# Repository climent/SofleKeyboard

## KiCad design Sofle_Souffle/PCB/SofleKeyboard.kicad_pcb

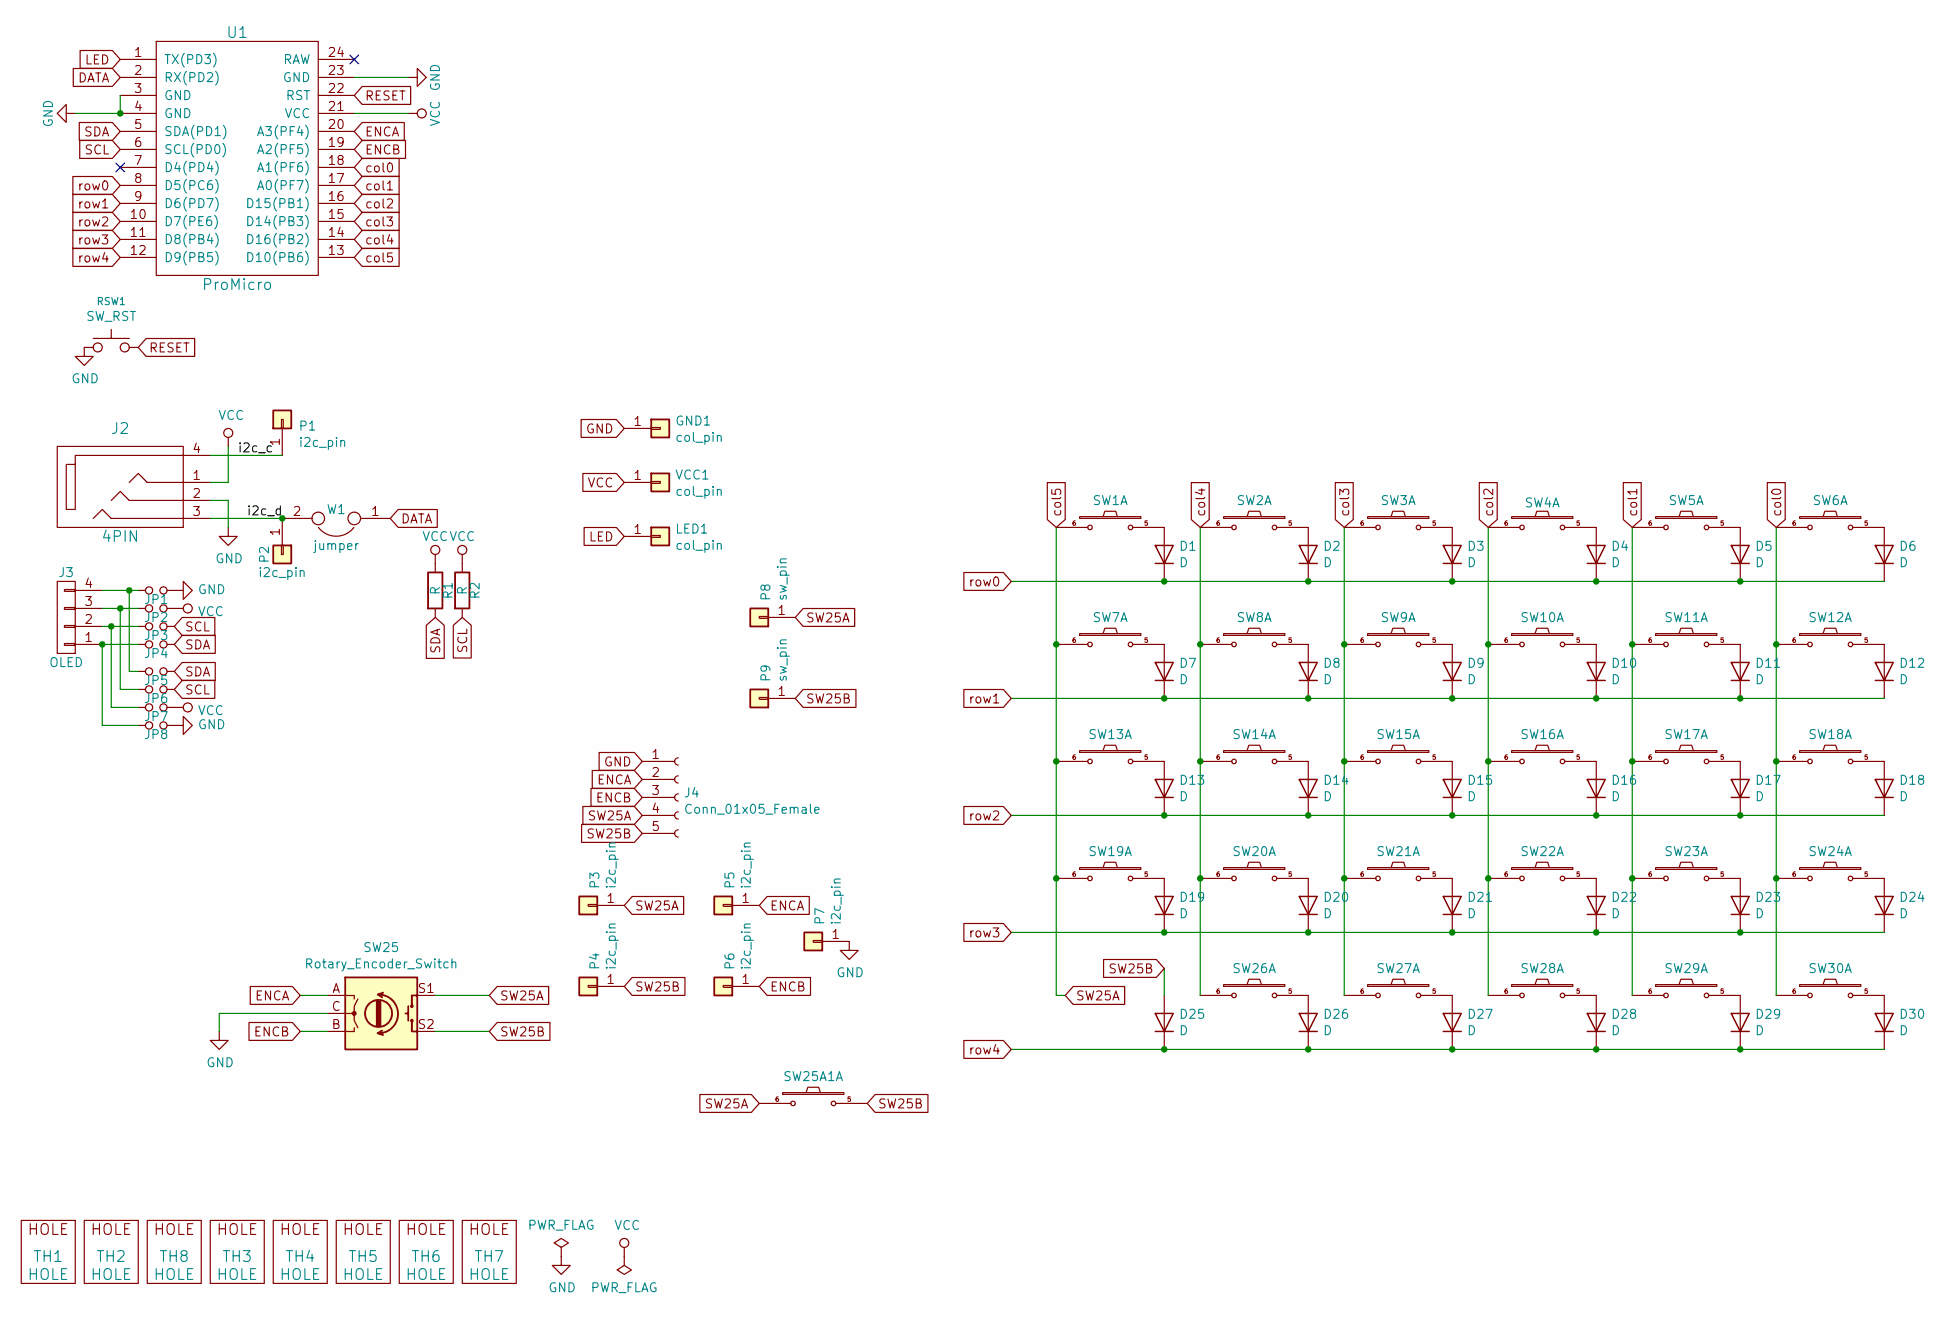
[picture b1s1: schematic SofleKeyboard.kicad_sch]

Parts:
D1, D2, D3, D4, D5, D6, D7, D8, D9, D10, D11, D12, D13, D14, D15, D16, D17, D18, D19, D20, D21, D22, D23, D24, D25, D26, D27, D28, D29, D30: D; crkbd-diode
GND1: col_pin; 1pin_conn
J2: 4PIN; MJ-4PP-9
J3: OLED; OLED_4Pin
J4: Conn_01x05_Female; PinHeader_1x05_P2.54mm_Horizontal
JP1, JP2, JP3, JP4, JP5, JP6, JP7, JP8: Jumper_NO_Small; Jumper
LED1: col_pin; 1pin_conn
P1, P2, P3, P4, P5, P6, P7: i2c_pin; 1pin_conn
P8, P9: sw_pin; Single_Hole
R1, R2: R; RESISTOR_mini
RSW1: SW_RST; TACT_SWITCH_TVBP06
SW1, SW2, SW3, SW4, SW5, SW6, SW7, SW8, SW9, SW10, SW11, SW12, SW13, SW14, SW15, SW16, SW17, SW18, SW19, SW20, SW21, SW22, SW23, SW24, SW25A1, SW26, SW27, SW28, SW29, SW30: SW_PUSH-MX_W_LED; SK6812MINI_and_cherry_NoLEDPads
SW25: Rotary_Encoder_Switch; RotaryEncoder_Alps_EC11E-Switch_Vertical_H20mm-keebio_modif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
TH1, TH2, TH8: HOLE; M2_HOLE_PCB
TH3, TH4, TH5, TH6, TH7: HOLE; HOLE_M2_TH
U1: ProMicro
VCC1: col_pin; 1pin_conn
W1: jumper; jumper_data

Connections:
/i2c_c: J2.4, P1.1; also elsewhere on the board
/i2c_d: J2.3, P2.1, W1.2; also elsewhere on the board
DATA: U1.2 (RX(PD2)), W1.1
ENCA: J4.2, P5.1, SW25.A, U1.20 (A3(PF4))
ENCB: J4.3, P6.1, SW25.B, U1.19 (A2(PF5))
GND: GND1.1, J2.2, J4.1, JP1.2, JP8.2, P7.1, RSW1.1, SW25.C, U1.3 (GND), U1.4 (GND), U1.23 (GND)
LED: LED1.1, U1.1 (TX(PD3))
unnamed: D1.2 (A), SW1.5
unnamed: D2.2 (A), SW2.5
unnamed: D3.2 (A), SW3.5
unnamed: D4.2 (A), SW4.5
unnamed: D5.2 (A), SW5.5
unnamed: D6.2 (A), SW6.5
unnamed: D7.2 (A), SW7.5
unnamed: D8.2 (A), SW8.5
unnamed: D9.2 (A), SW9.5
unnamed: D10.2 (A), SW10.5
unnamed: D11.2 (A), SW11.5
unnamed: D12.2 (A), SW12.5
unnamed: D13.2 (A), SW13.5
unnamed: D14.2 (A), SW14.5
unnamed: D15.2 (A), SW15.5
unnamed: D16.2 (A), SW16.5
unnamed: D17.2 (A), SW17.5
unnamed: D18.2 (A), SW18.5
unnamed: D19.2 (A), SW19.5
unnamed: D20.2 (A), SW20.5
unnamed: D21.2 (A), SW21.5
unnamed: D22.2 (A), SW22.5
unnamed: D23.2 (A), SW23.5
unnamed: D24.2 (A), SW24.5
unnamed: D26.2 (A), SW26.5
unnamed: D27.2 (A), SW27.5
unnamed: D28.2 (A), SW28.5
unnamed: D29.2 (A), SW29.5
unnamed: D30.2 (A), SW30.5
unnamed: J3.1, JP4.1, JP8.1
unnamed: J3.2, JP3.1, JP7.1
unnamed: J3.3, JP2.1, JP6.1
unnamed: J3.4, JP1.1, JP5.1
RESET: RSW1.2, U1.22 (RST)
SCL: JP3.2, JP6.2, R2.2, U1.6 (SCL(PD0)); also elsewhere on the board
SDA: JP4.2, JP5.2, R1.2, U1.5 (SDA(PD1)); also elsewhere on the board
SW25A: J4.4, P3.1, P8.1, SW1.6, SW7.6, SW13.6, SW19.6, SW25.S1, SW25A1.6, U1.13 (D10(PB6))
SW25B: D25.2 (A), J4.5, P4.1, P9.1, SW25.S2, SW25A1.5
VCC: J2.1, JP2.2, JP7.2, R1.1, R2.1, U1.21 (VCC), VCC1.1
col0: SW6.6, SW12.6, SW18.6, SW24.6, SW30.6, U1.18 (A1(PF6))
col1: SW5.6, SW11.6, SW17.6, SW23.6, SW29.6, U1.17 (A0(PF7))
col2: SW4.6, SW10.6, SW16.6, SW22.6, SW28.6, U1.16 (D15(PB1))
col3: SW3.6, SW9.6, SW15.6, SW21.6, SW27.6, U1.15 (D14(PB3))
col4: SW2.6, SW8.6, SW14.6, SW20.6, SW26.6, U1.14 (D16(PB2))
row0: D1.1 (K), D2.1 (K), D3.1 (K), D4.1 (K), D5.1 (K), D6.1 (K), U1.8 (D5(PC6))
row1: D7.1 (K), D8.1 (K), D9.1 (K), D10.1 (K), D11.1 (K), D12.1 (K), U1.9 (D6(PD7))
row2: D13.1 (K), D14.1 (K), D15.1 (K), D16.1 (K), D17.1 (K), D18.1 (K), U1.10 (D7(PE6))
row3: D19.1 (K), D20.1 (K), D21.1 (K), D22.1 (K), D23.1 (K), D24.1 (K), U1.11 (D8(PB4))
row4: D25.1 (K), D26.1 (K), D27.1 (K), D28.1 (K), D29.1 (K), D30.1 (K), U1.12 (D9(PB5))

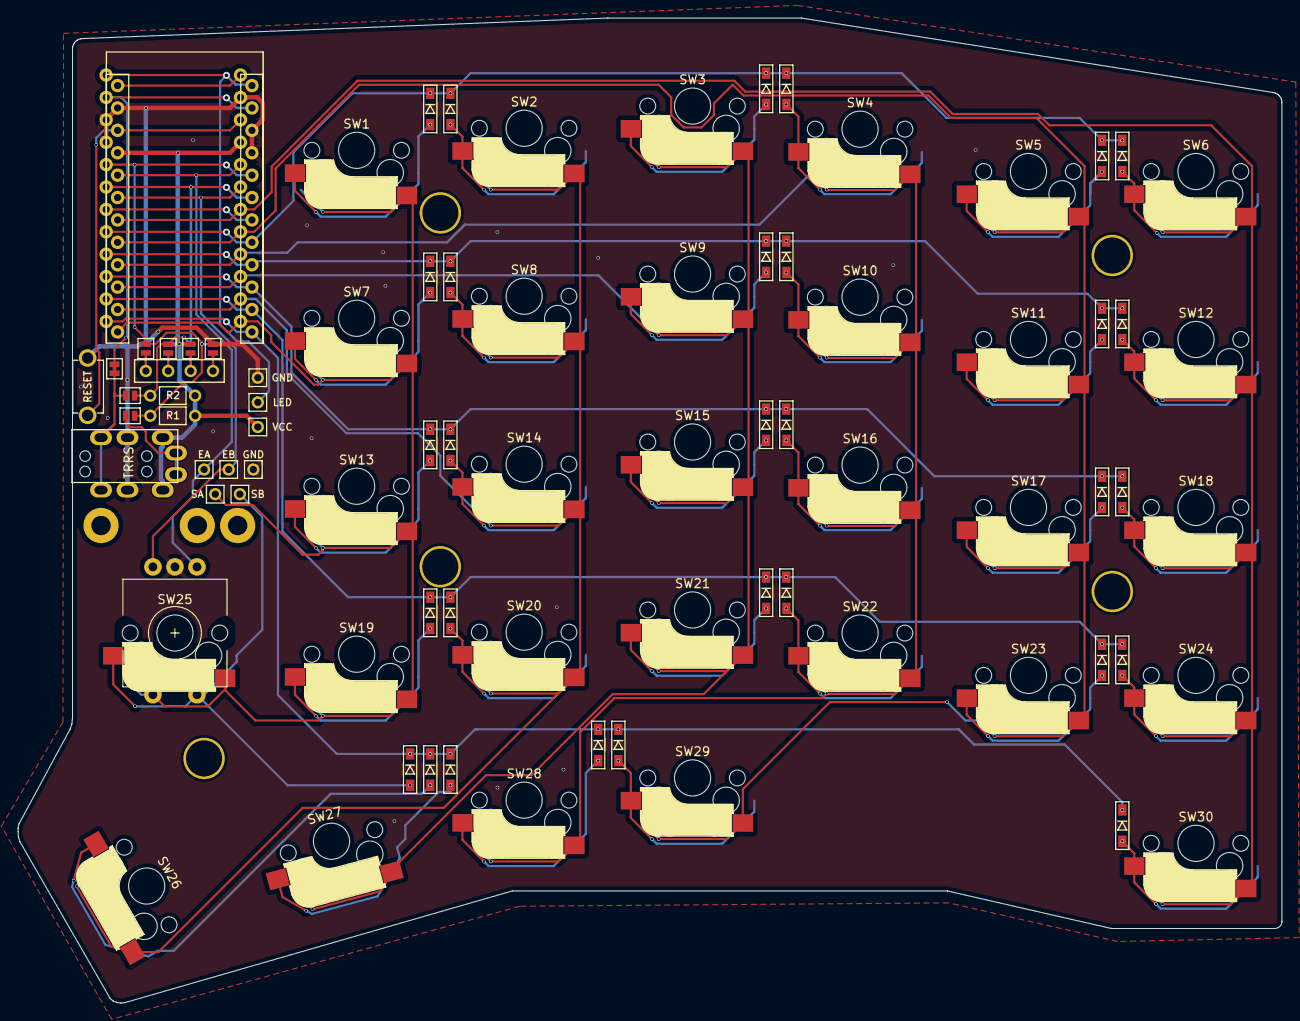
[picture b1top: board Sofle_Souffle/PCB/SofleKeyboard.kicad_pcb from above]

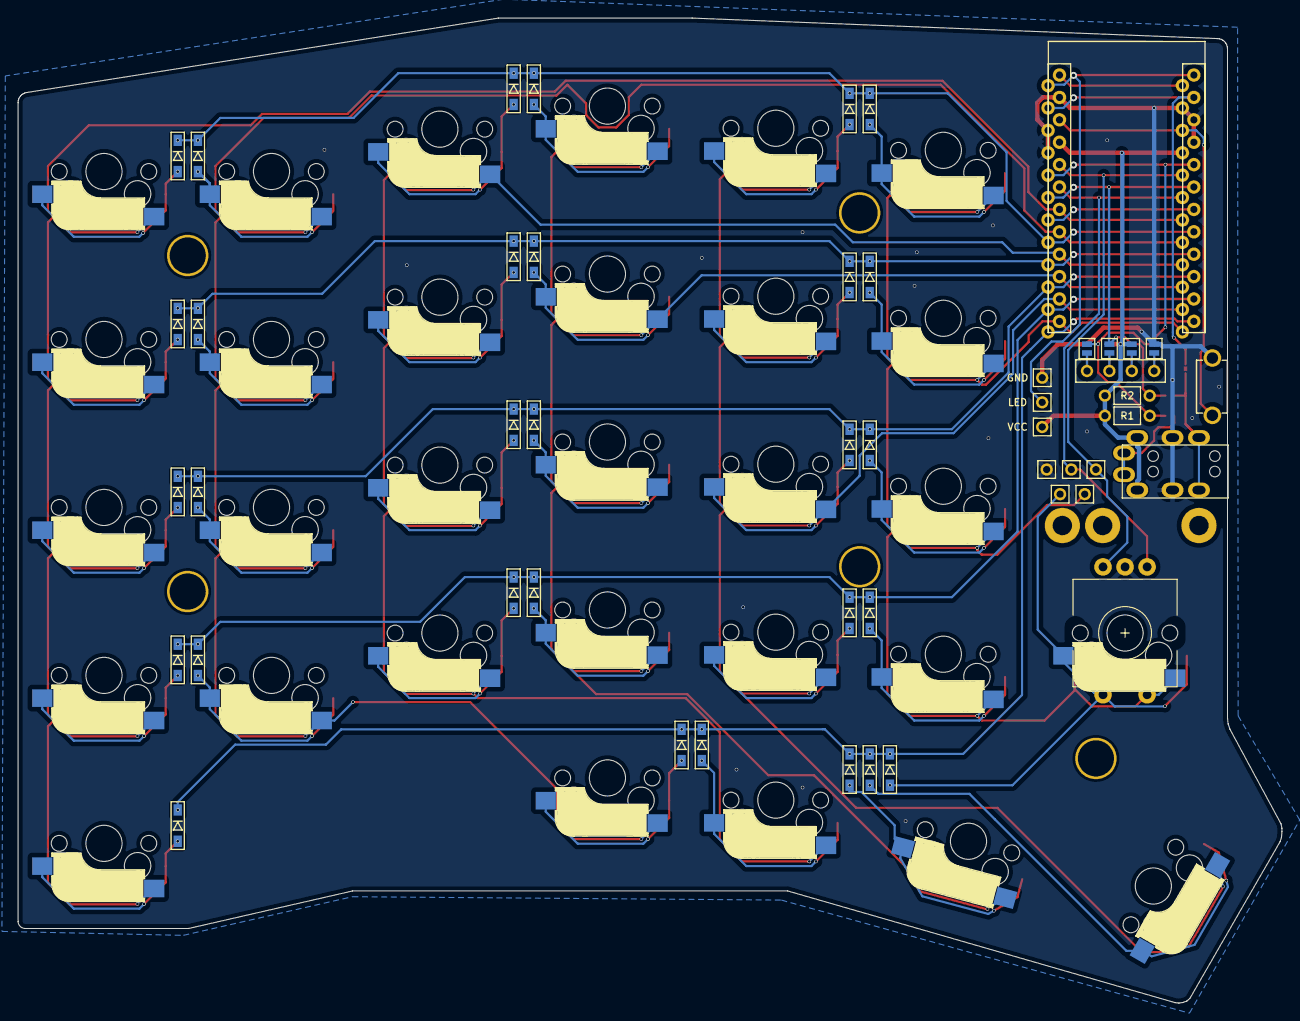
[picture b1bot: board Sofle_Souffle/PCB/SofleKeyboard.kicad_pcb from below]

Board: 2 copper layers, 143.3 x 111.7 mm, 94 parts (4 on the bottom side), 56 nets.

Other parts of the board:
JP9, JP10: SolderJumper_2_Open; Jumper

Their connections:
/i2c_c: JP9.1 (A); also elsewhere on the board
/i2c_d: JP10.1 (A); also elsewhere on the board
SCL: JP10.2 (B); also elsewhere on the board
SDA: JP9.2 (B); also elsewhere on the board

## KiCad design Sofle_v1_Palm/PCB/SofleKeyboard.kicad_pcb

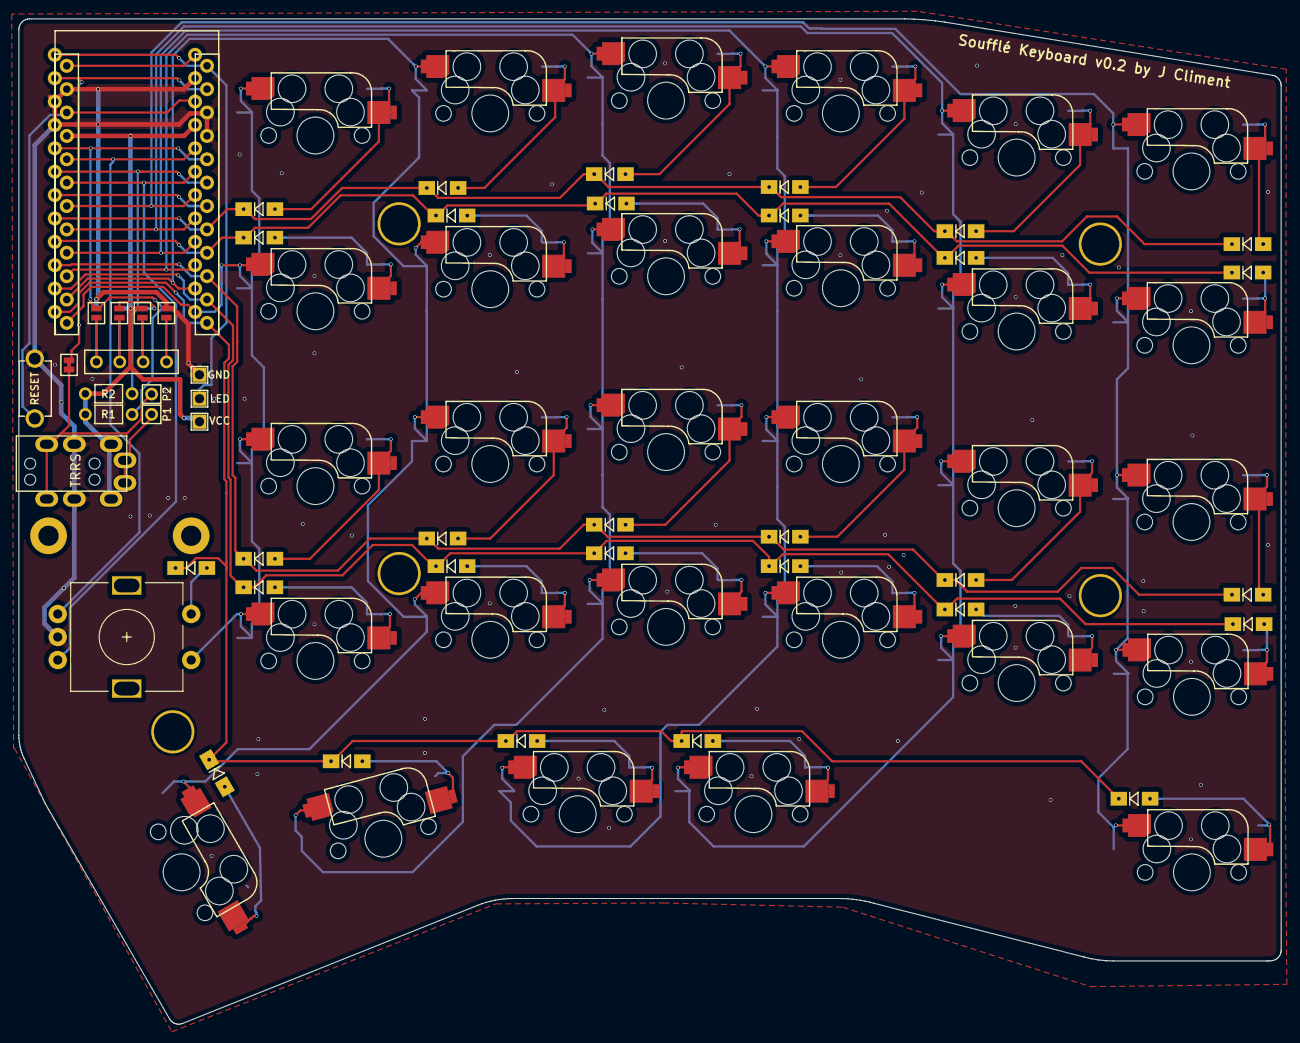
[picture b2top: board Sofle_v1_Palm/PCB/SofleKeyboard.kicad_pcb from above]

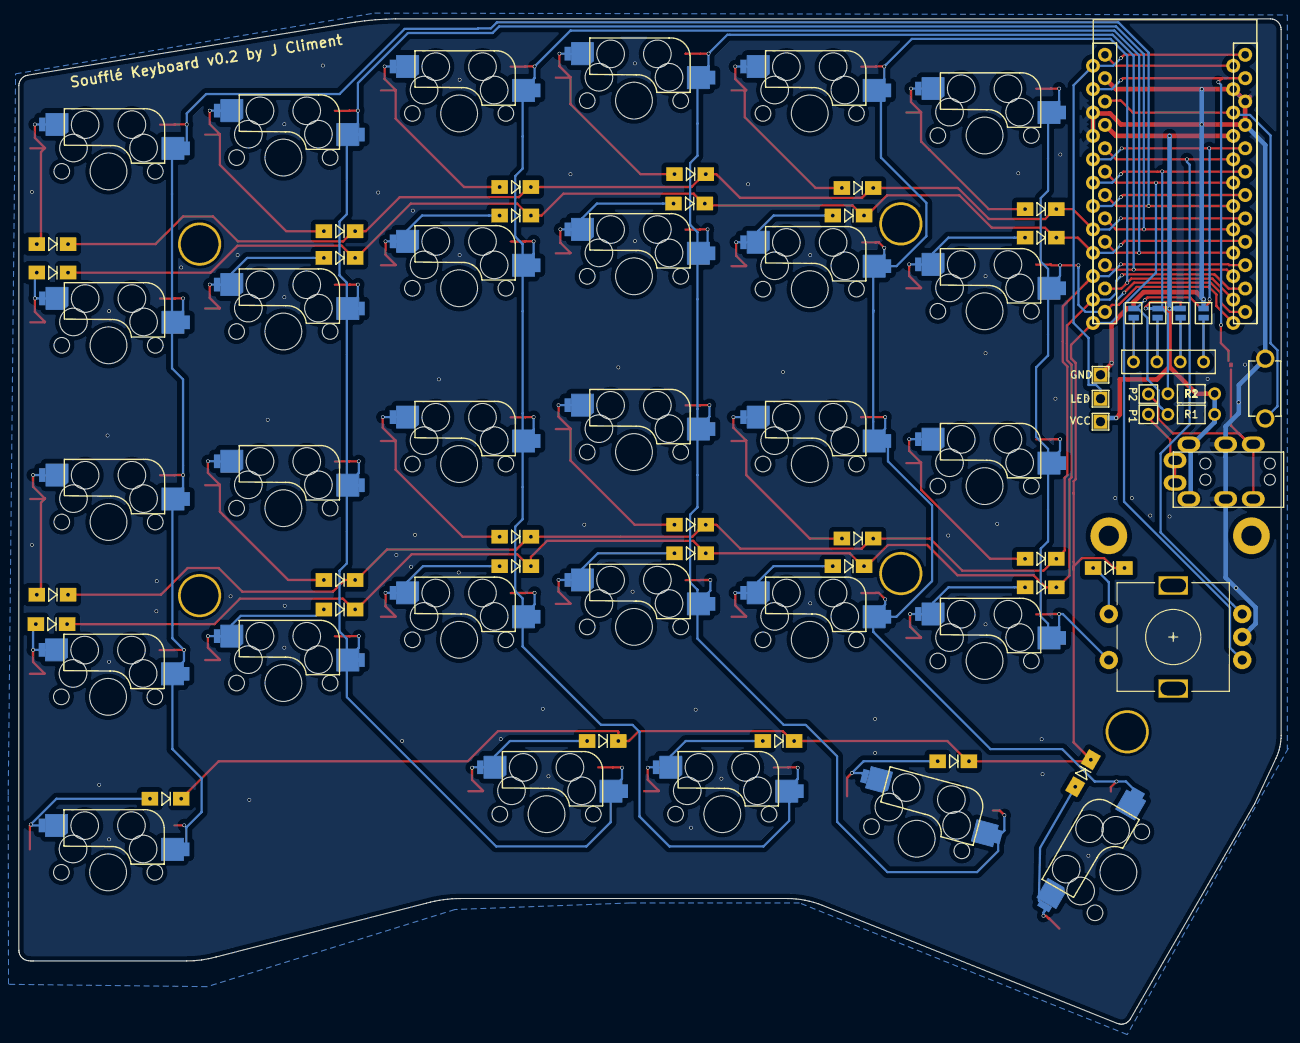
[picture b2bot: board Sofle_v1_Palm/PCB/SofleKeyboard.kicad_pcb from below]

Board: 2 copper layers, 137.2 x 109.2 mm, 85 parts (4 on the bottom side), 56 nets.

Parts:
D1, D2, D3, D4, D5, D6, D7, D8, D9, D10, D11, D12, D13, D14, D15, D16, D17, D18, D19, D20, D21, D22, D23, D24, D25, D26, D27, D28, D29, D30: D; Diode_SOD123
J1: LED
J2: 4PIN; MJ-4PP-9
J3: OLED; OLED_4Pin
JP1, JP2, JP3, JP4, JP5, JP6, JP7, JP8: Jumper_NO_Small; Jumper
P1, P2: i2c_pin; 1pin_conn
R1, R2: R; RESISTOR_mini
RSW1: SW_RST; TACT_SWITCH_TVBP06
SW1, SW2, SW3, SW4, SW5, SW6, SW7, SW8, SW9, SW10, SW11, SW12, SW13, SW14, SW15, SW16, SW17, SW18, SW19, SW20, SW21, SW22, SW23, SW24, SW27, SW28, SW29, SW30: SW_PUSH; CherryMX_Hotswap_mod
SW25: Rotary_Encoder_Switch; RotaryEncoder_Alps_EC11E-Switch_Vertical_H20mm-keebio_modif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
SW26: SW_PUSH; CherryMX_Hotswap_1.5_mod
TH1, TH2: HOLE; M2_HOLE_PCB
TH3, TH4, TH5, TH6, TH7: HOLE; HOLE_M2_TH
U1: ProMicro
W1: jumper; jumper_data

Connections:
/i2c_c: J2.4, P1.1
/i2c_d: J2.3, P2.1, W1.2
DATA: U1.2, W1.1
ENCA: SW25.A, U1.20
ENCB: SW25.B, U1.19
GND: J1.3, J2.2, JP1.2, JP8.2, RSW1.1, SW25.C, U1.3, U1.4, U1.23
LED: J1.2, U1.1
unnamed: D1.2, SW1.2
unnamed: D2.2, SW2.2
unnamed: D3.2, SW3.2
unnamed: D4.2, SW4.2
unnamed: D5.2, SW5.2
unnamed: D6.2, SW6.2
unnamed: D7.2, SW7.2
unnamed: D8.2, SW8.2
unnamed: D9.2, SW9.2
unnamed: D10.2, SW10.2
unnamed: D11.2, SW11.2
unnamed: D12.2, SW12.2
unnamed: D13.2, SW13.2
unnamed: D14.2, SW14.2
unnamed: D15.2, SW15.2
unnamed: D16.2, SW16.2
unnamed: D17.2, SW17.2
unnamed: D18.2, SW18.2
unnamed: D19.2, SW19.2
unnamed: D20.2, SW20.2
unnamed: D21.2, SW21.2
unnamed: D22.2, SW22.2
unnamed: D23.2, SW23.2
unnamed: D24.2, SW24.2
unnamed: D26.2, SW26.2
unnamed: D27.2, SW27.2
unnamed: D28.2, SW28.2
unnamed: D29.2, SW29.2
unnamed: D30.2, SW30.2
unnamed: J3.1, JP4.1, JP8.1
unnamed: J3.2, JP3.1, JP7.1
unnamed: J3.3, JP2.1, JP6.1
unnamed: J3.4, JP1.1, JP5.1
RESET: RSW1.2, U1.22
SCL: JP3.2, JP6.2, R2.2, U1.6
SDA: JP4.2, JP5.2, R1.2, U1.5
SW25A: SW1.1, SW7.1, SW13.1, SW19.1, SW25.S1, U1.13
SW25B: D25.2, SW25.S2
VCC: J1.1, J2.1, JP2.2, JP7.2, R1.1, R2.1, U1.21
col0: SW6.1, SW12.1, SW18.1, SW24.1, SW30.1, U1.18
col1: SW5.1, SW11.1, SW17.1, SW23.1, SW29.1, U1.17
col2: SW4.1, SW10.1, SW16.1, SW22.1, SW28.1, U1.16
col3: SW3.1, SW9.1, SW15.1, SW21.1, SW27.1, U1.15
col4: SW2.1, SW8.1, SW14.1, SW20.1, SW26.1, U1.14
row0: D1.1, D2.1, D3.1, D4.1, D5.1, D6.1, U1.8
row1: D7.1, D8.1, D9.1, D10.1, D11.1, D12.1, U1.9
row2: D13.1, D14.1, D15.1, D16.1, D17.1, D18.1, U1.10
row3: D19.1, D20.1, D21.1, D22.1, D23.1, D24.1, U1.11
row4: D25.1, D26.1, D27.1, D28.1, D29.1, D30.1, U1.12

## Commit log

2021-12-01 Initial checkin of a board with palm keys.
2021-12-01 Updated URL for keebio submodule
2021-12-01 Palm key really added.
2021-12-01 Updated PCB for palm key.
2021-12-05 Modified Sofle RGB with the outside thumb key moved to the palm.
2021-12-05 Added submodule with pimoroni footprint.
2021-12-05 New symbols and footprints for Pimoroni and EVQWGD001.
2021-12-05 Updated libraries for local . Reroute path of palm area.
2021-12-13 Added new key for Case TOP.
2021-12-13 Added cache file to gitignore.
2021-12-21 Routed 5-pin connector to the palm area for the roller encoder.
2021-12-21 New gitignore bits.
2021-12-21 New Souffle PCB.
2021-12-21 New track added.
2021-12-22 Added palm version of the v1 sofle.
2021-12-23 Completed Soufflé board with palm key. Missing the roller encoder.
2021-12-23 Added macos ds_store files to gitignore.
2021-12-23 Fix labels for the RGB connector.
2021-12-23 Added bak files to gitignore.
2021-12-23 Added EVQWGD001 footprint.
2021-12-23 Added EVQWGD001 and 5pin to schematic, and 5pin to PCB.
2021-12-23 Updated PCB.
2021-12-24 Deleted bak file.
2021-12-24 Initial mod for the souffle top case.
2021-12-24 Local changes.
2021-12-24 Moved SW30 to the pinky bottom.
2021-12-25 Removed 5pin connector on the right side of the case/pcb.
2021-12-26 Added top case with EVWQGD001 encoder.
2021-12-27 Updated board to KiCad v6.
2021-12-28 Re-release of the gerber file with KiCad V5.
2022-01-01 Updated bottom plate and added SVG files for case creation.
2022-01-16 Moved the connector pins for the roller encoder.
2022-01-19 Added top and lower case PCB files.
2022-01-22 Moved roller encoder connectors to the same vertical location.
2022-01-23 Small updates on the PCB and case.
2022-01-28 Changed footprint to correct switch holes.
2022-01-29 Completed redesign of the roller encoder pins.
2022-01-29 Backup files dance.
2022-01-29 Corrected bottom plate.
2022-01-30 Checkpoint commit.
2022-01-30 Fixed top case hole.
2022-02-04 Soufflé checkpoint commit.
2022-02-24 Local checkpoint commit.
2022-02-24 Updated PCB with corrected trace.
2022-05-13 Case updates.
